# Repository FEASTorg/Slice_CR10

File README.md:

# 10A Current Reader Slice

10A Current Reader Slice for BREAD.

## Introduction

[Short introduction on the project.]

## Usage

[Explain how to use the project. Include examples and screenshots if applicable.]

## Documentation

Please refer to the [docs](/docs) for more info.

---

<div align="center">
  
</div>

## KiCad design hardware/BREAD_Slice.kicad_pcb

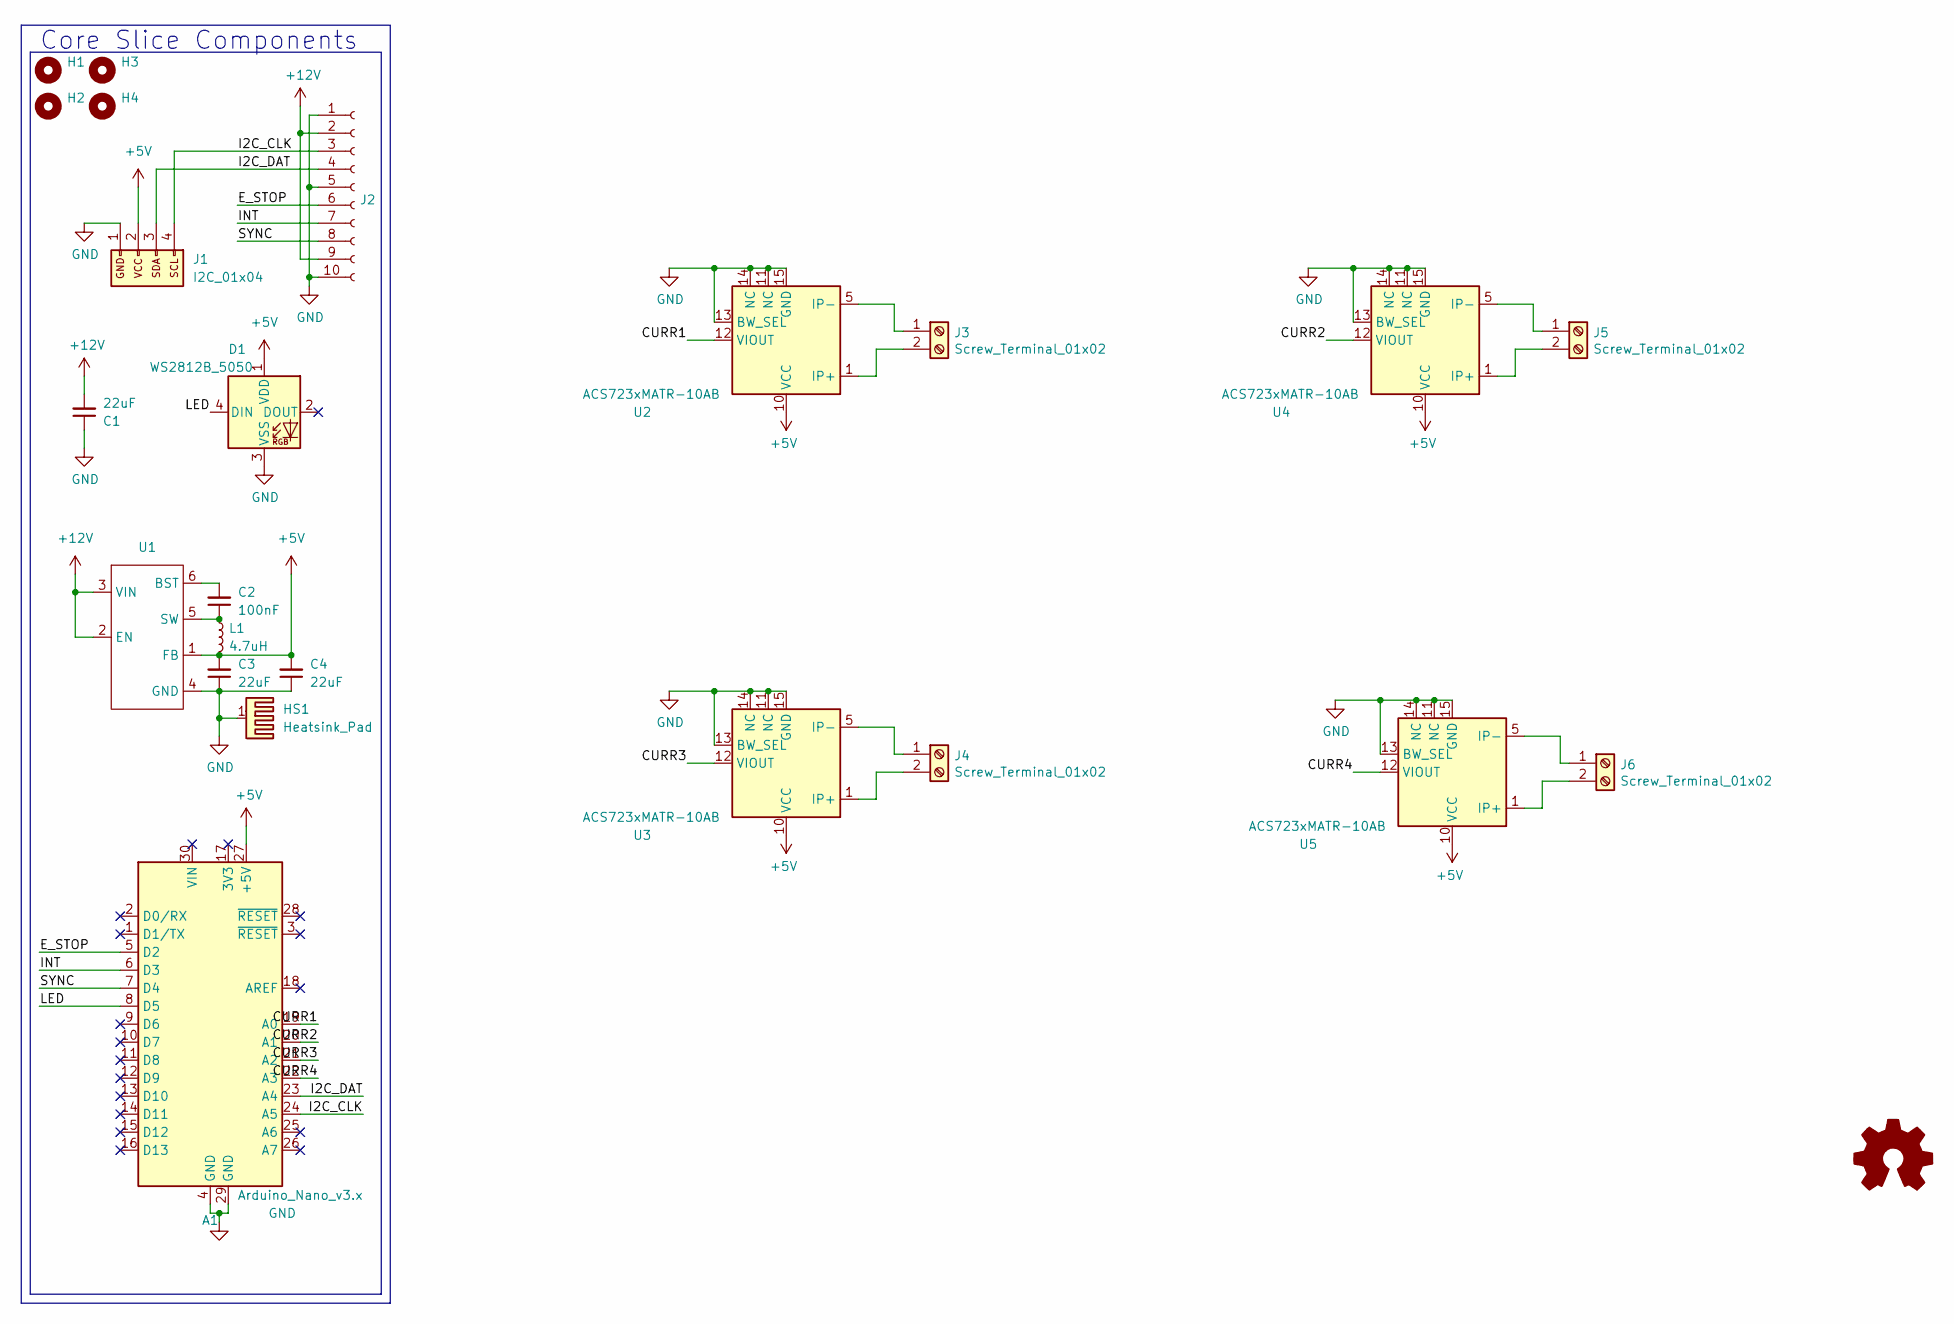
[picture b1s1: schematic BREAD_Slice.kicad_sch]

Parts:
A1: Arduino_Nano_v3.x; Arduino_Nano
C1, C3, C4: 22uF; C_1206_3216Metric
C2: 100nF; C_1206_3216Metric
D1: WS2812B_5050; WS2812-5050-4PIN
H1, H2, H3, H4: MountingHole; MountingHole_5mm
HS1: Heatsink_Pad; Thermal Pad
J1: I2C_01x04; JST_SH_SM04B-SRSS-TB_1x04-1MP_P1.00mm_Horizontal
J2: Conn_01x10_Female; PinSocket_1x10_P2.54mm_Horizontal
J3, J4, J5, J6: Screw_Terminal_01x02; Pheonix Conn Term TDPT 4 2-SP-6,35-ZB
L1: 4.7uH; L_1210_3225Metric
U1: TSOT-23-6
U2, U3, U4, U5: ACS723xMATR-10AB; SOIC-16W_7.5x10.3mm_P1.27mm

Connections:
+5V: A1.27 (+5V), C3.2, C4.2, D1.1 (VDD), J1.2, L1.2, U1.1 (FB), U2.10 (VCC), U3.10 (VCC), U4.10 (VCC), U5.10 (VCC)
+12V: C1.2, J2.2, J2.9, U1.2 (EN), U1.3 (VIN)
/CURR1: A1.19 (A0), U2.12 (VIOUT)
/CURR2: A1.20 (A1), U4.12 (VIOUT)
/CURR3: A1.21 (A2), U3.12 (VIOUT)
/CURR4: A1.22 (A3), U5.12 (VIOUT)
/E_STOP: A1.5 (D2), J2.6
/I2C_CLK: A1.24 (A5), J1.4, J2.3
/I2C_DAT: A1.23 (A4), J1.3, J2.4
/INT: A1.6 (D3), J2.7
/LED: A1.8 (D5), D1.4 (DIN)
/SYNC: A1.7 (D4), J2.8
GND: A1.4 (GND), A1.29 (GND), C1.1, C3.1, C4.1, D1.3 (VSS), HS1.1, J1.1, J2.1, J2.5, J2.10, U1.4 (GND), U2.11 (NC), U2.13 (BW_SEL), U2.14 (NC), U2.15 (GND), U3.11 (NC), U3.13 (BW_SEL), U3.14 (NC), U3.15 (GND), U4.11 (NC), U4.13 (BW_SEL), U4.14 (NC), U4.15 (GND), U5.11 (NC), U5.13 (BW_SEL), U5.14 (NC), U5.15 (GND)
unnamed: J3.1, U2.5 (IP-), U2.6 (IP-), U2.7 (IP-), U2.8 (IP-)
unnamed: J3.2, U2.1 (IP+), U2.2 (IP+), U2.3 (IP+), U2.4 (IP+)
unnamed: J4.1, U3.5 (IP-), U3.6 (IP-), U3.7 (IP-), U3.8 (IP-)
unnamed: J4.2, U3.1 (IP+), U3.2 (IP+), U3.3 (IP+), U3.4 (IP+)
unnamed: J5.1, U4.5 (IP-), U4.6 (IP-), U4.7 (IP-), U4.8 (IP-)
unnamed: J5.2, U4.1 (IP+), U4.2 (IP+), U4.3 (IP+), U4.4 (IP+)
unnamed: J6.1, U5.5 (IP-), U5.6 (IP-), U5.7 (IP-), U5.8 (IP-)
unnamed: J6.2, U5.1 (IP+), U5.2 (IP+), U5.3 (IP+), U5.4 (IP+)
unnamed: C2.2, U1.6 (BST)
unnamed: C2.1, L1.1, U1.5 (SW)

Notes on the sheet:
Core Slice Components

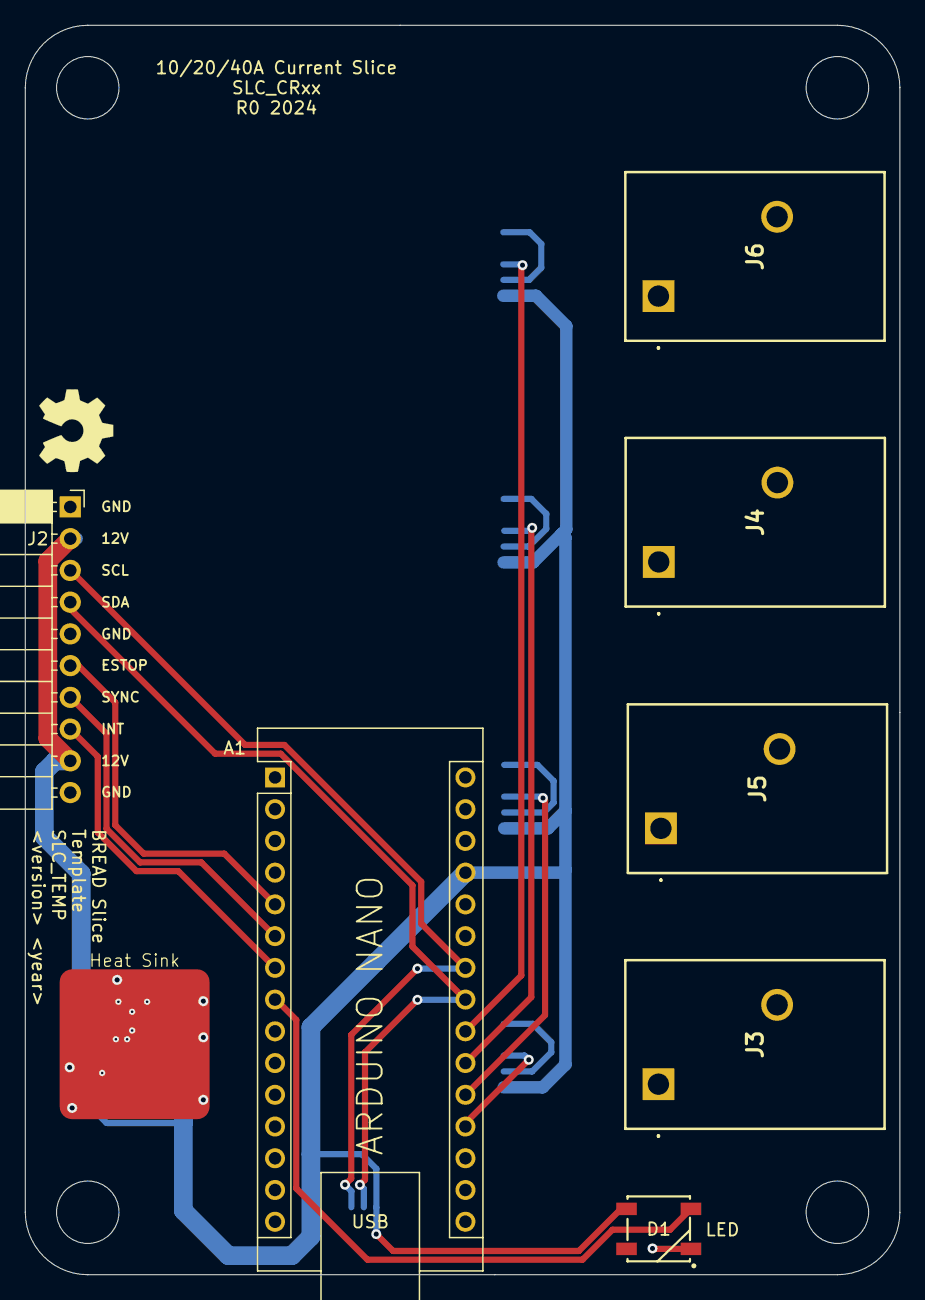
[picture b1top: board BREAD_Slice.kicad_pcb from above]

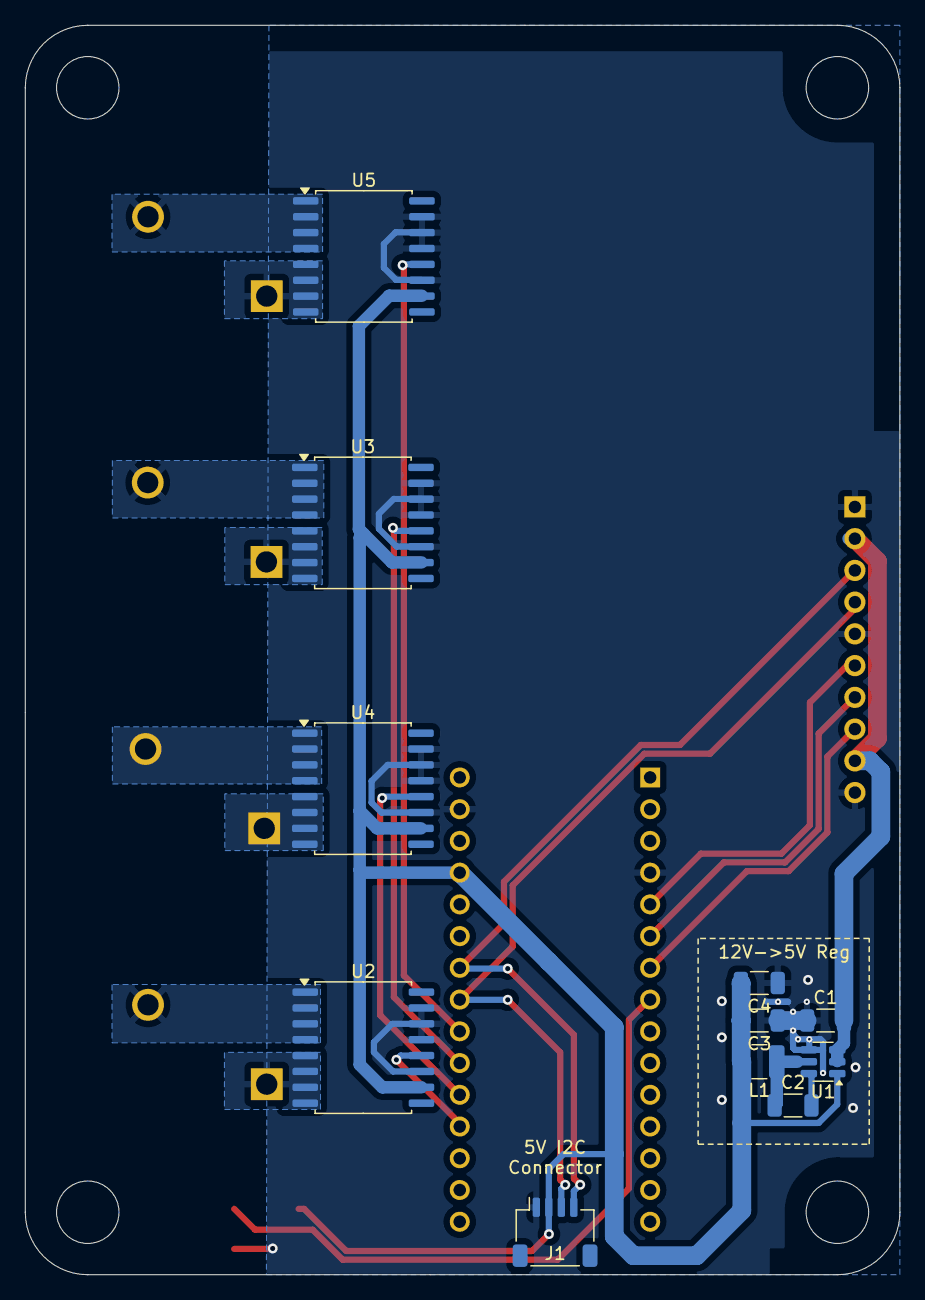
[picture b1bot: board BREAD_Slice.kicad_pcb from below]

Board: 2 copper layers, 70.0 x 100.0 mm, 24 parts (11 on the bottom side), 23 nets.

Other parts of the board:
Logo1: Logo_Open_Hardware_Small; OSHW-Symbol_6.7x6mm_SilkScreen

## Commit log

2024-08-16 updated to new BREAD format
2024-08-16 removed legacy hardware
2024-08-16 updated for CRxx forking
